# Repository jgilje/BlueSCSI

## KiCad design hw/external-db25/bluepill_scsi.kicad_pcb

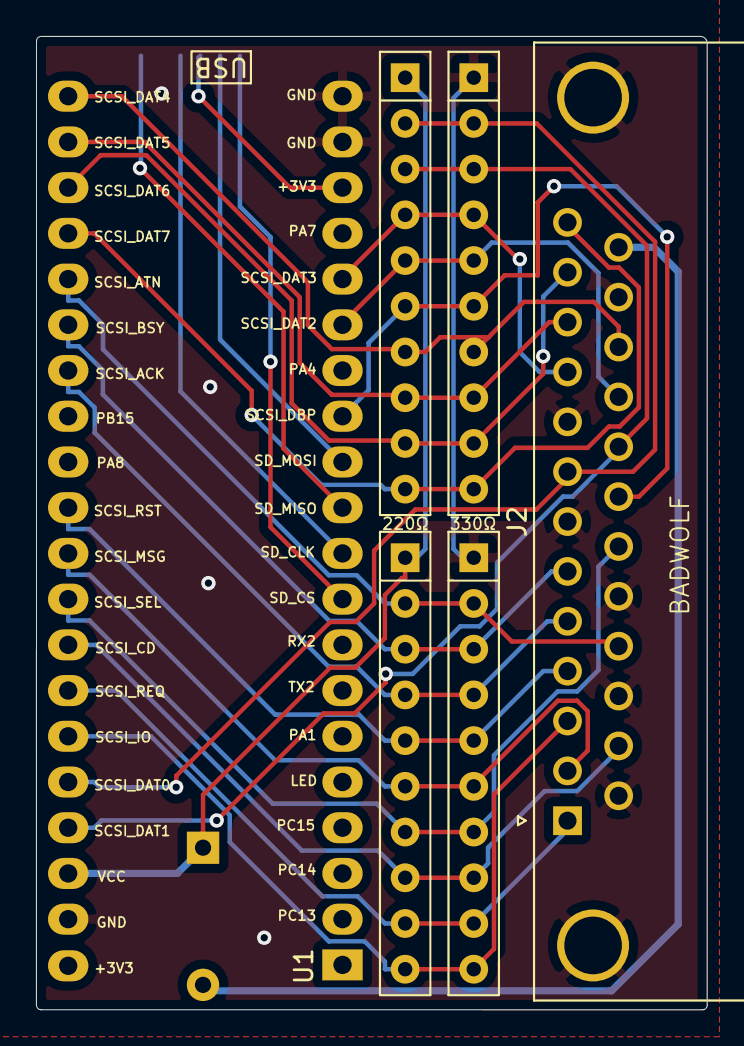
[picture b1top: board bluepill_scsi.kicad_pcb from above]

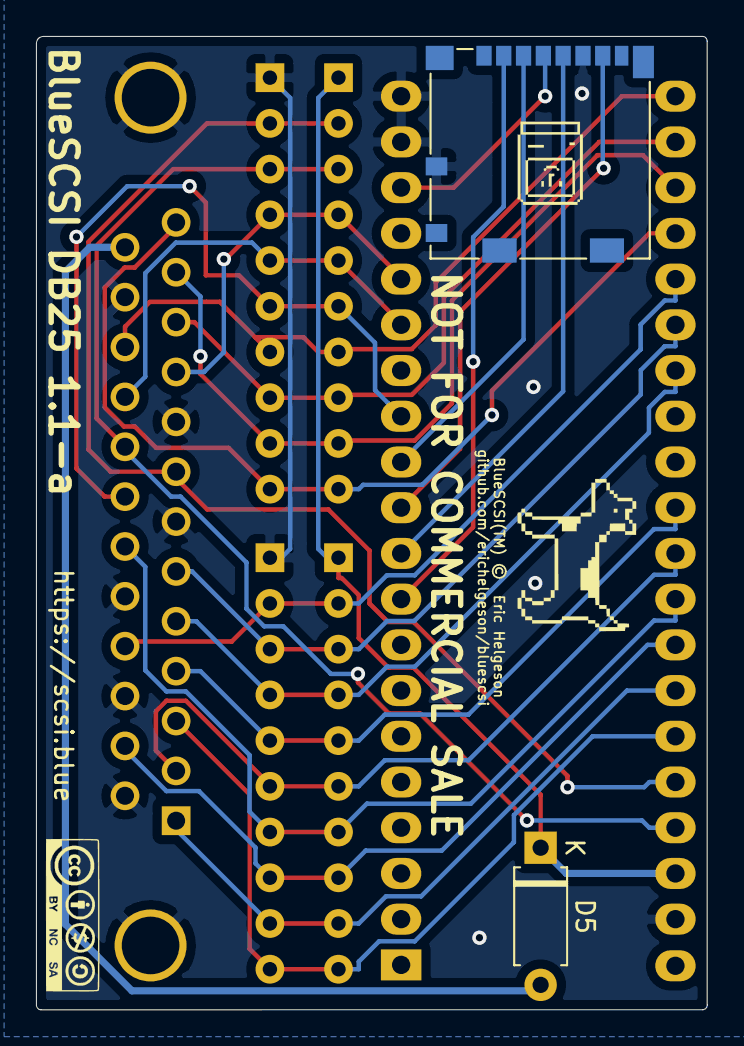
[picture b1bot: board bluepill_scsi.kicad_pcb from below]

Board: 2 copper layers, 37.3 x 54.1 mm, 11 parts (5 on the bottom side), 26 nets.

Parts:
D5: Diode; D_A-405_P7.62mm_Horizontal
G001: LOGO; dogcow
G002: LOGO; cc_by_nc_sa_front_silk_screen
G004: LOGO; mac_happy_small
J2: DB25_Male_MountingHoles; DSUB-25_Male_Horizontal_P2.77x2.84mm_EdgePinOffset7.70mm_Ho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
J5: Micro_SD_Card; microSD_HC_Molex_104031-0811
RN1, RN3: 220; R_Array_SIP10
RN2, RN4: 330; R_Array_SIP10
U1: BluePill_STM32F103C

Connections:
+3V3: J5.4, U1.18, U1.40
/SCSI_ACK: J2.5, RN3.4, RN4.4, U1.27
/SCSI_ATN: J2.17, RN3.2, RN4.2, U1.25
/SCSI_BSY: J2.6, RN3.3, RN4.3, U1.26
/SCSI_CD: J2.15, RN3.8, RN4.8, U1.33
/SCSI_DAT0: J2.8, RN1.2, RN2.2, U1.36
/SCSI_DAT1: J2.21, RN1.3, RN2.3, U1.37
/SCSI_DAT2: J2.22, RN1.5, RN2.5, U1.15
/SCSI_DAT3: J2.10, RN1.4, RN2.4, U1.16
/SCSI_DAT4: J2.23, RN1.7, RN2.7, U1.21
/SCSI_DAT5: J2.11, RN1.8, RN2.8, U1.22
/SCSI_DAT6: J2.12, RN1.9, RN2.9, U1.23
/SCSI_DAT7: J2.13, RN1.10, RN2.10, U1.24
/SCSI_DBP: J2.20, RN1.6, RN2.6, U1.13
/SCSI_IO: J2.3, RN3.10, RN4.10, U1.35
/SCSI_MSG: J2.2, RN3.6, RN4.6, U1.31
/SCSI_REQ: J2.1, RN3.9, RN4.9, U1.34
/SCSI_RST: J2.4, RN3.5, RN4.5, U1.30
/SCSI_SEL: J2.19, RN3.7, RN4.7, U1.32
/SD_CLK: J5.5, U1.10
/SD_CS: J5.2, U1.9
/SD_MISO: J5.7, U1.11
/SD_MOSI: J5.3, U1.12
/TERM_PWR: D5.2, J2.25
GND: J2.0, J2.7, J2.9, J2.14, J2.16, J2.18, J2.24, J5.6, J5.9, RN2.1, RN4.1, U1.19, U1.20, U1.39
VCC: D5.1, RN1.1, RN3.1, U1.38

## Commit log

2021-12-19 Update footprint to Connector_Dsub:DSUB-25_Male_Horizontal_P2.77x2.84mm_EdgePinOffset7.70mm_Housed_MountingHolesOffset9.12mm to make vertical mounting easier
2022-03-30 v1.1-BETA-20220330
2022-06-02 Release/Reserve Commands
2022-06-10 onInquiryCommand(): return unsupported logical unit for both Peripheral Qualifier and Peripheral Device Type if lun is undefined. prevents 8 identical luns appearing on sparcstations

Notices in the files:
hw/external-db25/bluepill_scsi.kicad_pcb:
BlueSCSI(TM) ©  Eric Helgeson
